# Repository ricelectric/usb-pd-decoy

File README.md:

# usb-pd-decoy

This is an open source repository for a USB PD decoy module using CH224K. More information is available [here](https://qiita.com/ricelectric/items/8ef598b7e089e5330fd7).

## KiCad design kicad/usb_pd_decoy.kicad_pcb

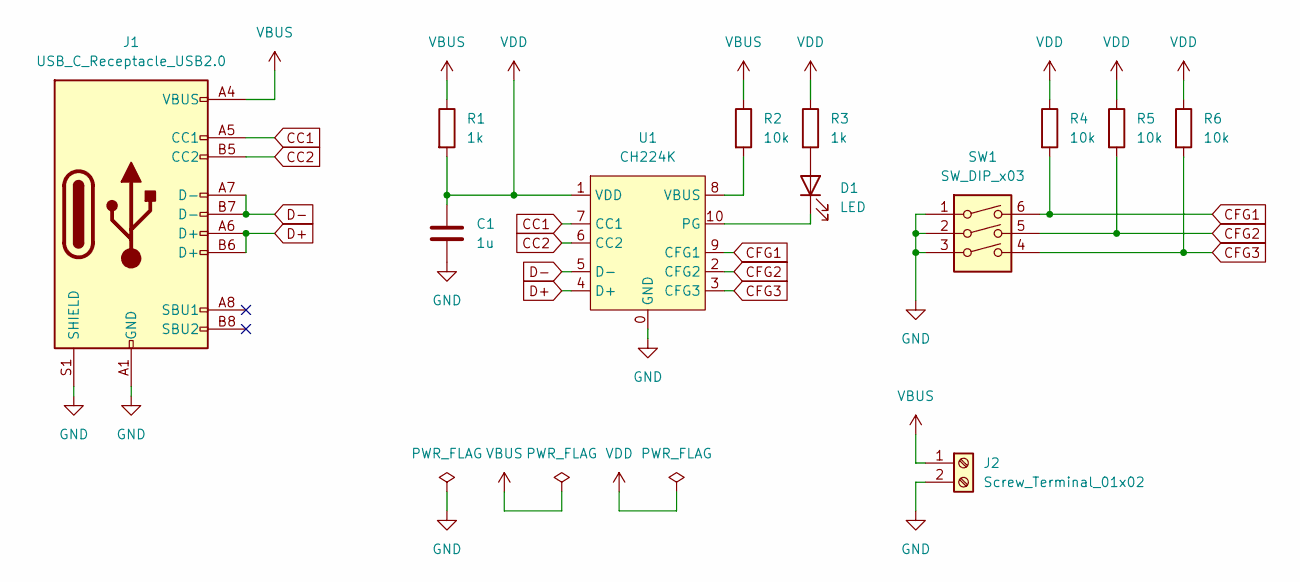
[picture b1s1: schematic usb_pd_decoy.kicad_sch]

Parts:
C1: 1u; C_0603_1608Metric
D1: LED; LED_0603_1608Metric
J1: USB_C_Receptacle_USB2.0; USB_C_Receptacle_XKB_U262-16XN-4BVC11
J2: Screw_Terminal_01x02; TerminalBlock_Phoenix_MKDS-1,5-2-5.08_1x02_P5.08mm_Horizont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
R1: 1k; R_2512_6332Metric
R2, R4, R5, R6: 10k; R_0603_1608Metric
R3: 1k; R_0603_1608Metric
SW1: SW_DIP_x03; SW_DIP_SPSTx03_Slide_7.5x9.6mm_W7.62mm_P2.54mm
U1: CH224K; ESSOP-10_3.9x4.9mm_P1.00mm

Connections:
CC1: J1.A5 (CC1), U1.7 (CC1)
CC2: J1.B5 (CC2), U1.6 (CC2)
CFG1: R4.2, SW1.6, U1.9 (CFG1)
CFG2: R5.2, SW1.5, U1.2 (CFG2)
CFG3: R6.2, SW1.4, U1.3 (CFG3)
D+: J1.A6 (D+), J1.B6 (D+), U1.4 (D+)
D-: J1.A7 (D-), J1.B7 (D-), U1.5 (D-)
GND: C1.2, J1.A1 (GND), J1.A12 (GND), J1.B1 (GND), J1.B12 (GND), J1.S1 (SHIELD), J2.2, SW1.1, SW1.2, SW1.3, U1.0 (GND)
unnamed: D1.1 (K), U1.10 (PG)
unnamed: D1.2 (A), R3.2
unnamed: R2.2, U1.8 (VBUS)
VBUS: J1.A4 (VBUS), J1.A9 (VBUS), J1.B4 (VBUS), J1.B9 (VBUS), J2.1, R1.1, R2.1
VDD: C1.1, R1.2, R3.1, R4.1, R5.1, R6.1, U1.1 (VDD)

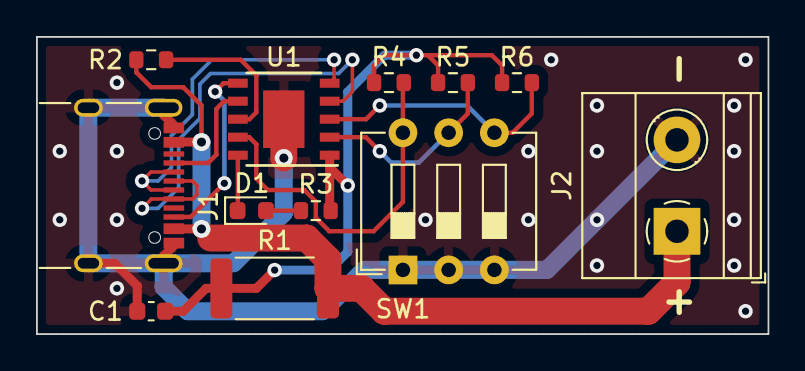
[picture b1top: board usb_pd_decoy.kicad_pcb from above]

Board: 2 copper layers, 40.6 x 16.5 mm, 12 parts (0 on the bottom side), 13 nets.

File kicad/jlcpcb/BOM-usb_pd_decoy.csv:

Comment,Designator,Footprint,LCSC
1u,C1,C_0603_1608Metric,C15849
1k,R3,R_0603_1608Metric,C21190
10k,"R2,R4,R5,R6",R_0603_1608Metric,C25804
USB_C_Receptacle_USB2.0,J1,USB_C_Receptacle_XKB_U262-16XN-4BVC11,C2988369
PWR,D1,LED_0603_1608Metric,C72041
CH224K,U1,ESSOP-10_3.9x4.9mm_P1.00mm,C970725
SW_DIP_x03,SW1,SW_DIP_SPSTx03_Slide_7.5x9.6mm_W7.62mm_P2.54mm,
Screw_Terminal_01x02,J2,"TerminalBlock_Phoenix_MKDS-1,5-2-5.08_1x02_P5.08mm_Horizontal",
1k,R1,R_2512_6332Metric,
